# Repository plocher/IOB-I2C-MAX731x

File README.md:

# IOB-I2C-MAX731x
## License: CERN Open Hardware Licence v1.2

IOB I2C MAX7311/7318 based IO Expander

The MAX 731x series costs twice that of the MCP23017/PCA9555 expanders; for that price one gets support for  up to 64x devices on a single I2C chain.

### Specifications

This board is based on the MAX7311/7318 16 bit IO Expander, which supports up to 64x instances.

Each board provides a latched set of 16x IO points, with each point
being software selectable to be either an input or an output. The
individual points are reasonably protected from the environment, and can
sink 10 mA each (they are NOT current sources!)
By using active low inputs and outputs, the effects of environmental noise are
reduced - remote sensors only need to ground an I/O point to register
activity.

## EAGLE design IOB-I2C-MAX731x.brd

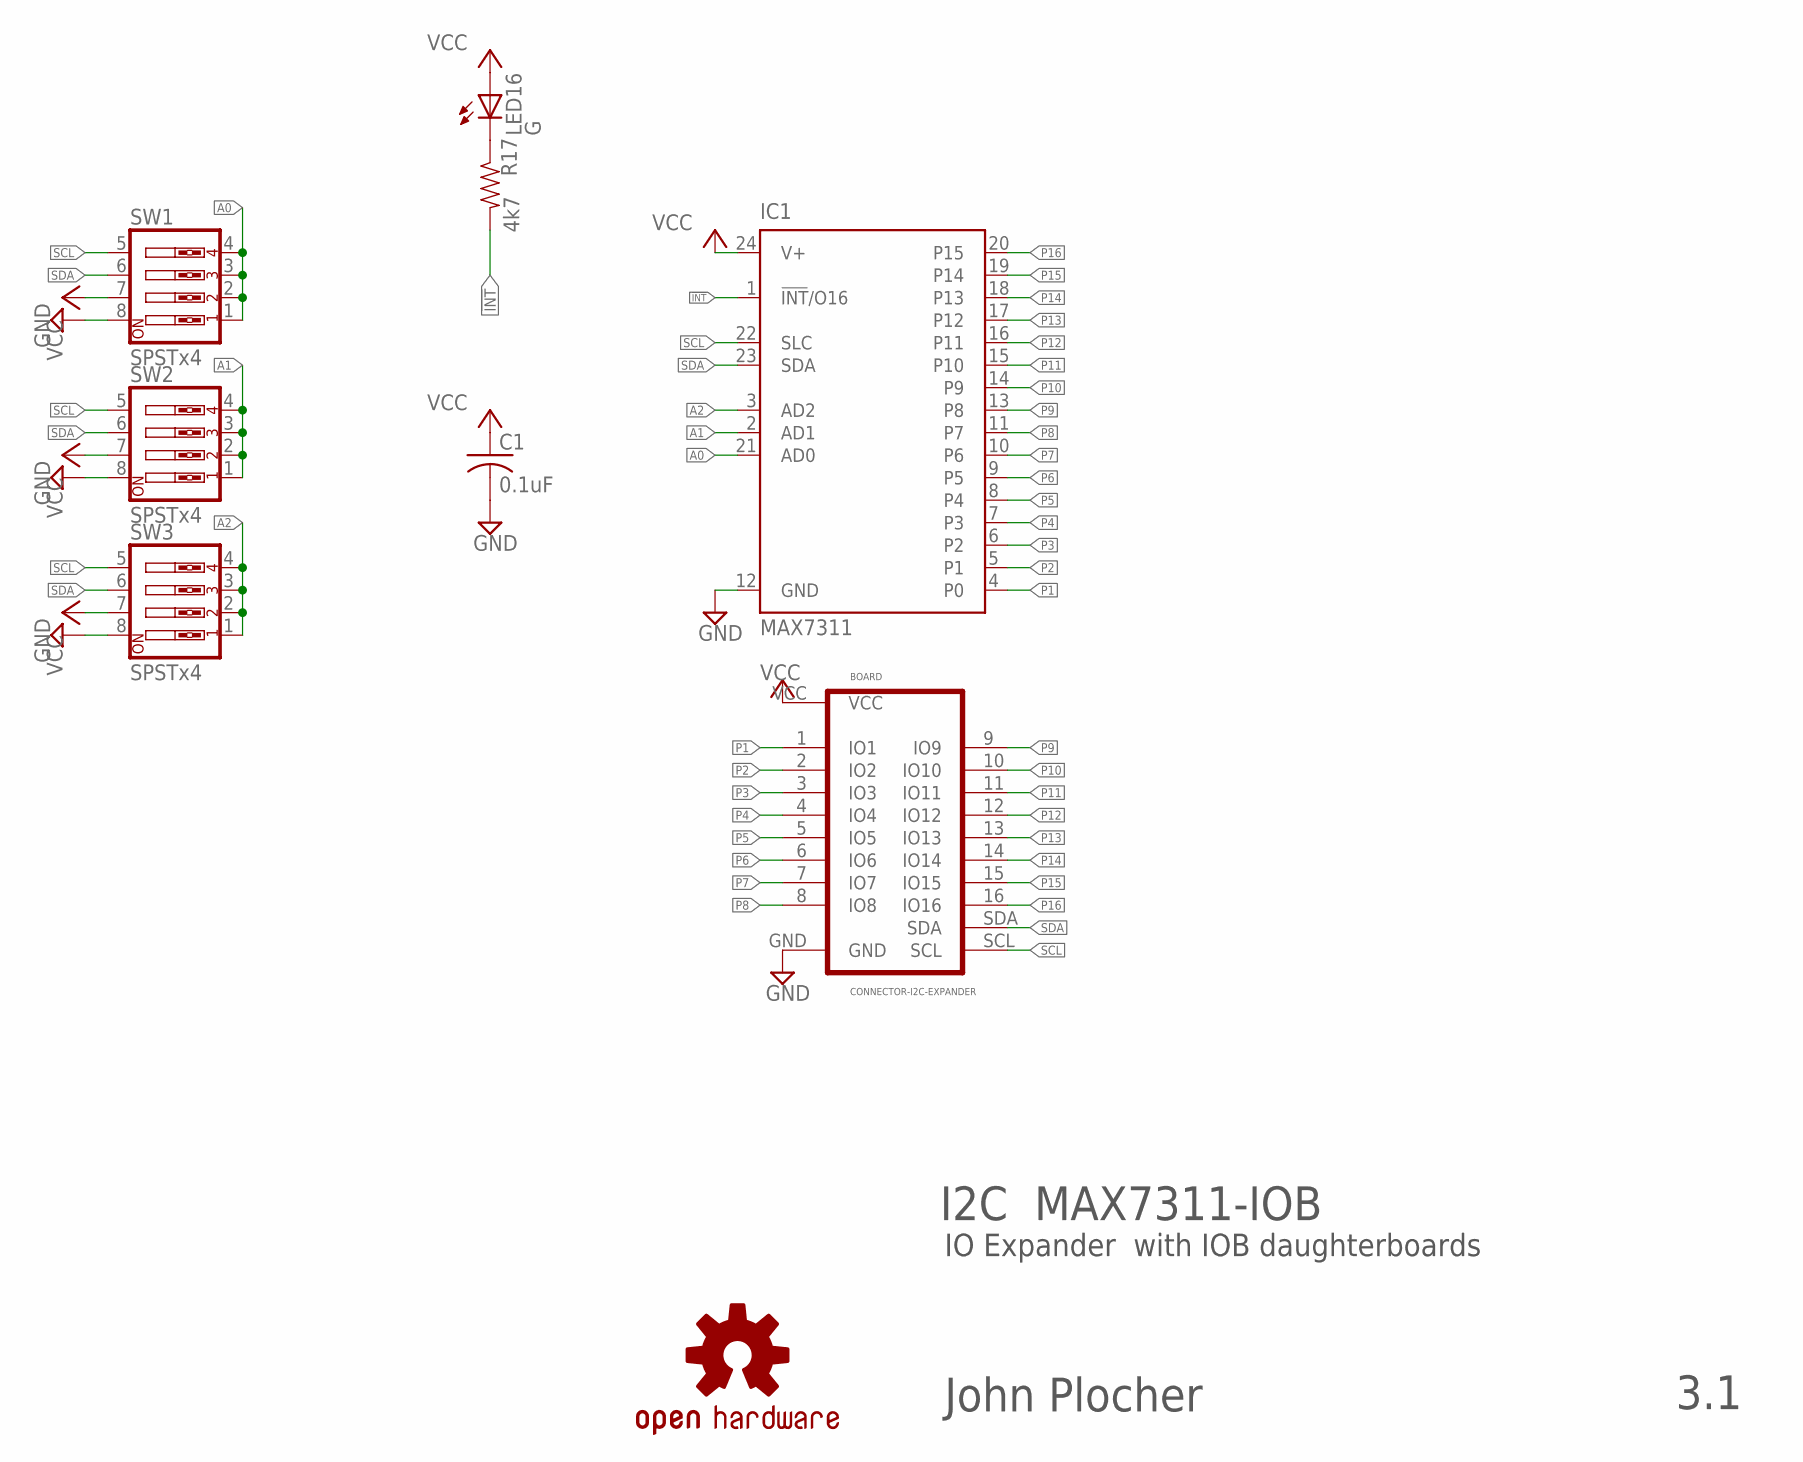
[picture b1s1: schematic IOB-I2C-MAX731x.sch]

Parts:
BOARD: CONNECTOR-I2C-EXPANDER; I2C-EXPANDER
C1: 0.1uF; 0603-CAP
IC1: MAX7311; TSSOP24
LED16: G; 0603-LED
R17: 4k7; 0603-RES
SW1, SW2, SW3: SPSTx4; EDG-04
U$1: OSHW; OSHW-LOGO-L

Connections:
!INT: IC1.1 (!INT!/O16), R17.2
A0: IC1.21 (AD0), SW1.1, SW1.2, SW1.3, SW1.4
A1: IC1.2 (AD1), SW2.1, SW2.2, SW2.3, SW2.4
A2: IC1.3 (AD2), SW3.1, SW3.2, SW3.3, SW3.4
GND: BOARD.GND, C1.2, IC1.12 (GND), SW1.8, SW2.8, SW3.8
unnamed: LED16.C, R17.1
P1: BOARD.1 (IO1), IC1.4 (P0)
P2: BOARD.2 (IO2), IC1.5 (P1)
P3: BOARD.3 (IO3), IC1.6 (P2)
P4: BOARD.4 (IO4), IC1.7 (P3)
P5: BOARD.5 (IO5), IC1.8 (P4)
P6: BOARD.6 (IO6), IC1.9 (P5)
P7: BOARD.7 (IO7), IC1.10 (P6)
P8: BOARD.8 (IO8), IC1.11 (P7)
P9: BOARD.9 (IO9), IC1.13 (P8)
P10: BOARD.10 (IO10), IC1.14 (P9)
P11: BOARD.11 (IO11), IC1.15 (P10)
P12: BOARD.12 (IO12), IC1.16 (P11)
P13: BOARD.13 (IO13), IC1.17 (P12)
P14: BOARD.14 (IO14), IC1.18 (P13)
P15: BOARD.15 (IO15), IC1.19 (P14)
P16: BOARD.16 (IO16), IC1.20 (P15)
SCL: BOARD.SCL, IC1.22 (SLC), SW1.5, SW2.5, SW3.5
SDA: BOARD.SDA, IC1.23 (SDA), SW1.6, SW2.6, SW3.6
VCC: BOARD.VCC, C1.1, IC1.24 (V+), LED16.A, SW1.7, SW2.7, SW3.7

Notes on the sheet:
I2C MAX7311-IOB
IO Expander with IOB daughterboards
John Plocher
3.1

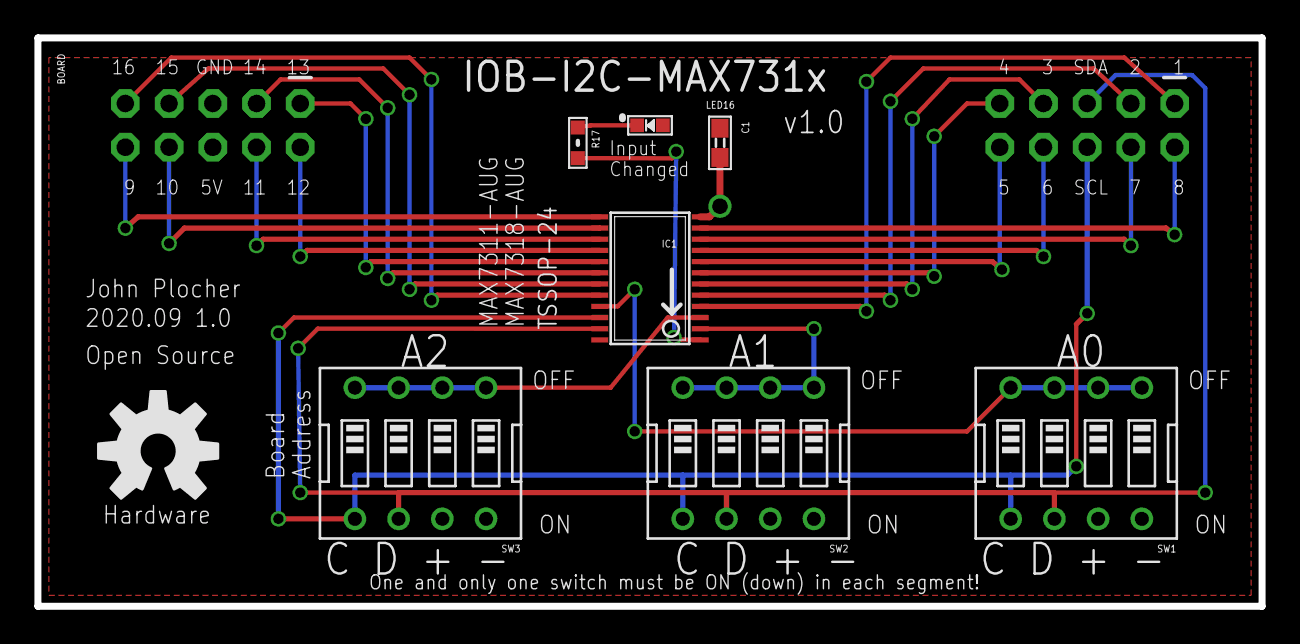
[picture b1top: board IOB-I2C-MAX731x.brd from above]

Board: 2 copper layers, 71.1 x 33.0 mm, 9 parts (0 on the bottom side), 25 nets.

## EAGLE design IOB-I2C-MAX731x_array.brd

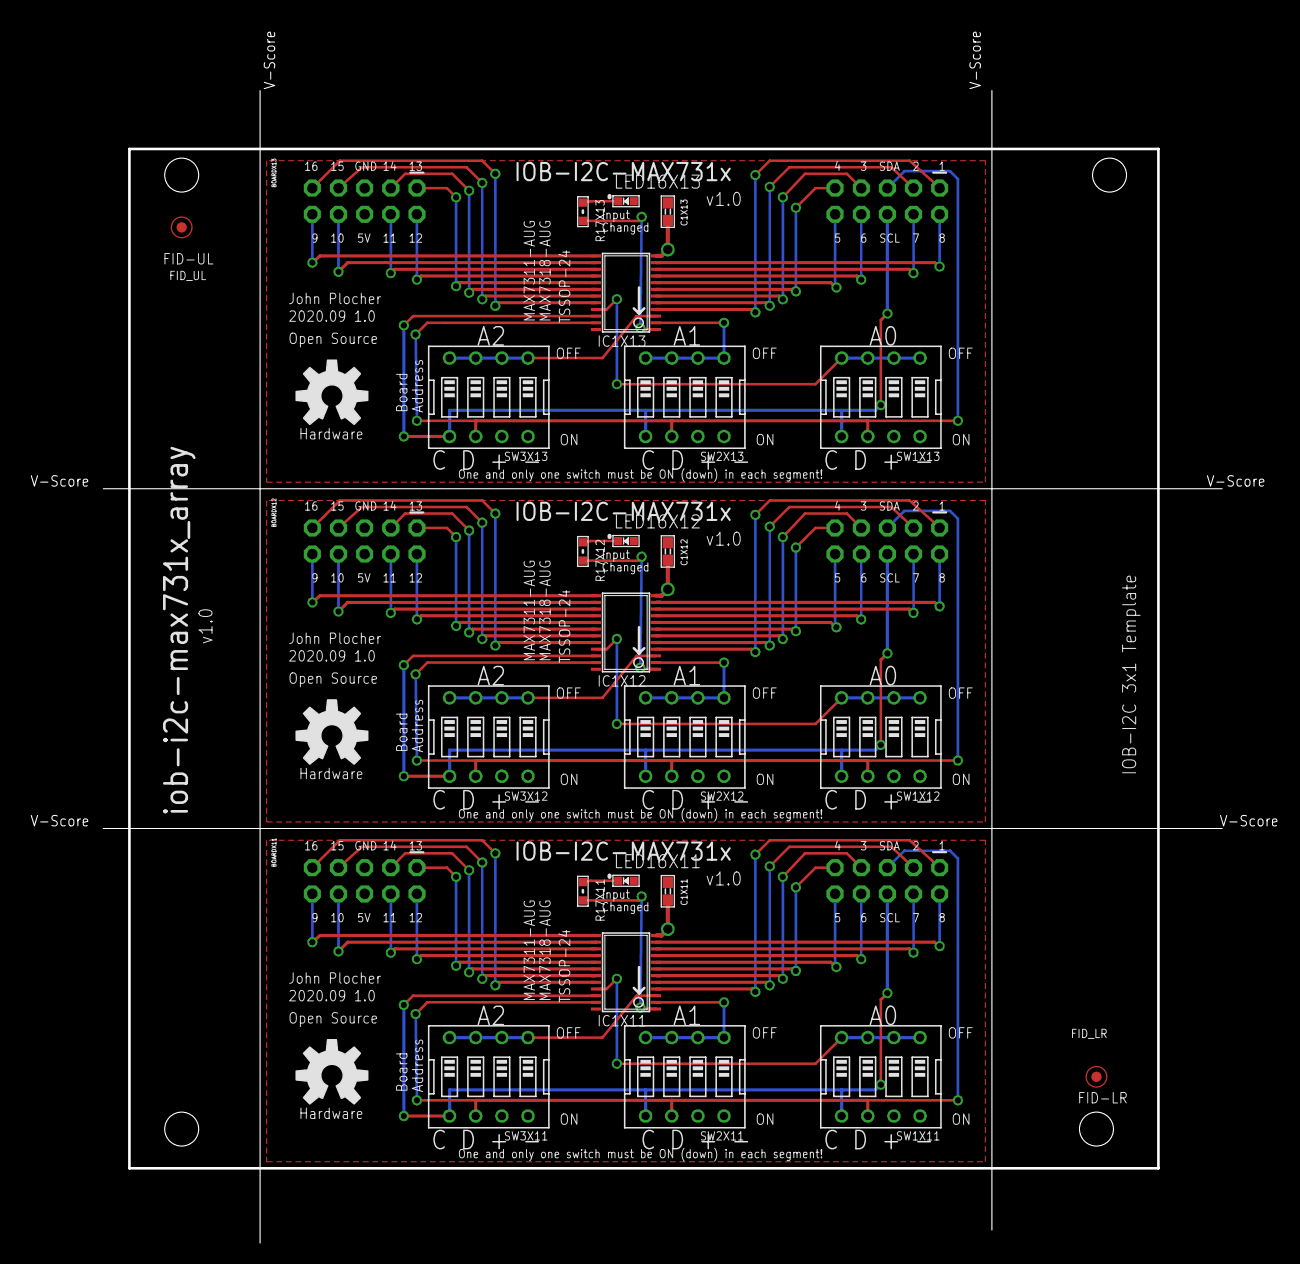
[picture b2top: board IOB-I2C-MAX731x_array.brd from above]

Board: 2 copper layers, 122.1 x 118.6 mm, 30 parts (0 on the bottom side), 75 nets.

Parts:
BOARDX11, BOARDX12, BOARDX13: CONNECTOR-I2C-EXPANDER; I2C-EXPANDER
C1X11, C1X12, C1X13: 0.1uF; 0603-CAP
FID-LR: FIDUCIAL; FIDUCIAL_1MM
FID-UL: FIDUCIAL; FIDUCIAL_1MM
IC1X11, IC1X12, IC1X13: MAX7311; TSSOP24
LED16X11, LED16X12, LED16X13: G; 0603-LED
R17X11, R17X12, R17X13: 4k7; 0603-RES
SW1X11, SW1X12, SW1X13, SW2X11, SW2X12, SW2X13, SW3X11, SW3X12, SW3X13: SPSTx4; EDG-04
U$1X11, U$1X12, U$1X13: DOC-OSHW-LOGO-L; OSHW-LOGO-L
U$5X1: BOARD; BOARD-TEMPLATE-IOB-I2C-3X1-ARRAY

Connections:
!INTX11: IC1X11.1, R17X11.2
!INTX12: IC1X12.1, R17X12.2
!INTX13: IC1X13.1, R17X13.2
A0X11: IC1X11.21, SW1X11.1, SW1X11.2, SW1X11.3, SW1X11.4
A0X12: IC1X12.21, SW1X12.1, SW1X12.2, SW1X12.3, SW1X12.4
A0X13: IC1X13.21, SW1X13.1, SW1X13.2, SW1X13.3, SW1X13.4
A1X11: IC1X11.2, SW2X11.1, SW2X11.2, SW2X11.3, SW2X11.4
A1X12: IC1X12.2, SW2X12.1, SW2X12.2, SW2X12.3, SW2X12.4
A1X13: IC1X13.2, SW2X13.1, SW2X13.2, SW2X13.3, SW2X13.4
A2X11: IC1X11.3, SW3X11.1, SW3X11.2, SW3X11.3, SW3X11.4
A2X12: IC1X12.3, SW3X12.1, SW3X12.2, SW3X12.3, SW3X12.4
A2X13: IC1X13.3, SW3X13.1, SW3X13.2, SW3X13.3, SW3X13.4
GNDX11: BOARDX11.GND, C1X11.2, IC1X11.12, SW1X11.8, SW2X11.8, SW3X11.8
GNDX12: BOARDX12.GND, C1X12.2, IC1X12.12, SW1X12.8, SW2X12.8, SW3X12.8
GNDX13: BOARDX13.GND, C1X13.2, IC1X13.12, SW1X13.8, SW2X13.8, SW3X13.8
unnamed: LED16X11.C, R17X11.1
unnamed: LED16X12.C, R17X12.1
unnamed: LED16X13.C, R17X13.1
P1X11: BOARDX11.1, IC1X11.4
P1X12: BOARDX12.1, IC1X12.4
P1X13: BOARDX13.1, IC1X13.4
P2X11: BOARDX11.2, IC1X11.5
P2X12: BOARDX12.2, IC1X12.5
P2X13: BOARDX13.2, IC1X13.5
P3X11: BOARDX11.3, IC1X11.6
P3X12: BOARDX12.3, IC1X12.6
P3X13: BOARDX13.3, IC1X13.6
P4X11: BOARDX11.4, IC1X11.7
P4X12: BOARDX12.4, IC1X12.7
P4X13: BOARDX13.4, IC1X13.7
P5X11: BOARDX11.5, IC1X11.8
P5X12: BOARDX12.5, IC1X12.8
P5X13: BOARDX13.5, IC1X13.8
P6X11: BOARDX11.6, IC1X11.9
P6X12: BOARDX12.6, IC1X12.9
P6X13: BOARDX13.6, IC1X13.9
P7X11: BOARDX11.7, IC1X11.10
P7X12: BOARDX12.7, IC1X12.10
P7X13: BOARDX13.7, IC1X13.10
P8X11: BOARDX11.8, IC1X11.11
P8X12: BOARDX12.8, IC1X12.11
P8X13: BOARDX13.8, IC1X13.11
P9X11: BOARDX11.9, IC1X11.13
P9X12: BOARDX12.9, IC1X12.13
P9X13: BOARDX13.9, IC1X13.13
P10X11: BOARDX11.10, IC1X11.14
P10X12: BOARDX12.10, IC1X12.14
P10X13: BOARDX13.10, IC1X13.14
P11X11: BOARDX11.11, IC1X11.15
P11X12: BOARDX12.11, IC1X12.15
P11X13: BOARDX13.11, IC1X13.15
P12X11: BOARDX11.12, IC1X11.16
P12X12: BOARDX12.12, IC1X12.16
P12X13: BOARDX13.12, IC1X13.16
P13X11: BOARDX11.13, IC1X11.17
P13X12: BOARDX12.13, IC1X12.17
P13X13: BOARDX13.13, IC1X13.17
P14X11: BOARDX11.14, IC1X11.18
P14X12: BOARDX12.14, IC1X12.18
P14X13: BOARDX13.14, IC1X13.18
P15X11: BOARDX11.15, IC1X11.19
P15X12: BOARDX12.15, IC1X12.19
P15X13: BOARDX13.15, IC1X13.19
P16X11: BOARDX11.16, IC1X11.20
P16X12: BOARDX12.16, IC1X12.20
P16X13: BOARDX13.16, IC1X13.20
SCLX11: BOARDX11.SCL, IC1X11.22, SW1X11.5, SW2X11.5, SW3X11.5
SCLX12: BOARDX12.SCL, IC1X12.22, SW1X12.5, SW2X12.5, SW3X12.5
SCLX13: BOARDX13.SCL, IC1X13.22, SW1X13.5, SW2X13.5, SW3X13.5
SDAX11: BOARDX11.SDA, IC1X11.23, SW1X11.6, SW2X11.6, SW3X11.6
SDAX12: BOARDX12.SDA, IC1X12.23, SW1X12.6, SW2X12.6, SW3X12.6
SDAX13: BOARDX13.SDA, IC1X13.23, SW1X13.6, SW2X13.6, SW3X13.6
VCCX11: BOARDX11.VCC, C1X11.1, IC1X11.24, LED16X11.A, SW1X11.7, SW2X11.7, SW3X11.7
VCCX12: BOARDX12.VCC, C1X12.1, IC1X12.24, LED16X12.A, SW1X12.7, SW2X12.7, SW3X12.7
VCCX13: BOARDX13.VCC, C1X13.1, IC1X13.24, LED16X13.A, SW1X13.7, SW2X13.7, SW3X13.7

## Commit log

2020-09-04 Initial version
2020-09-05 cleanup
2020-09-11 cleanup layout
2020-09-11 update docs
2020-09-12 cleanup docs
2020-10-05 added values for connectors
2020-10-06 normalized values

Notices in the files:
parts and their libraries:
SPCoast: http://freedomdefined.org/OSHW Creative Commons - Attribution - ShareAlike 3.0
